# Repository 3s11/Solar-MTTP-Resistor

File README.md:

# Solar-MTTP-Resistor
Photovoltaic heater at the maximum available power.

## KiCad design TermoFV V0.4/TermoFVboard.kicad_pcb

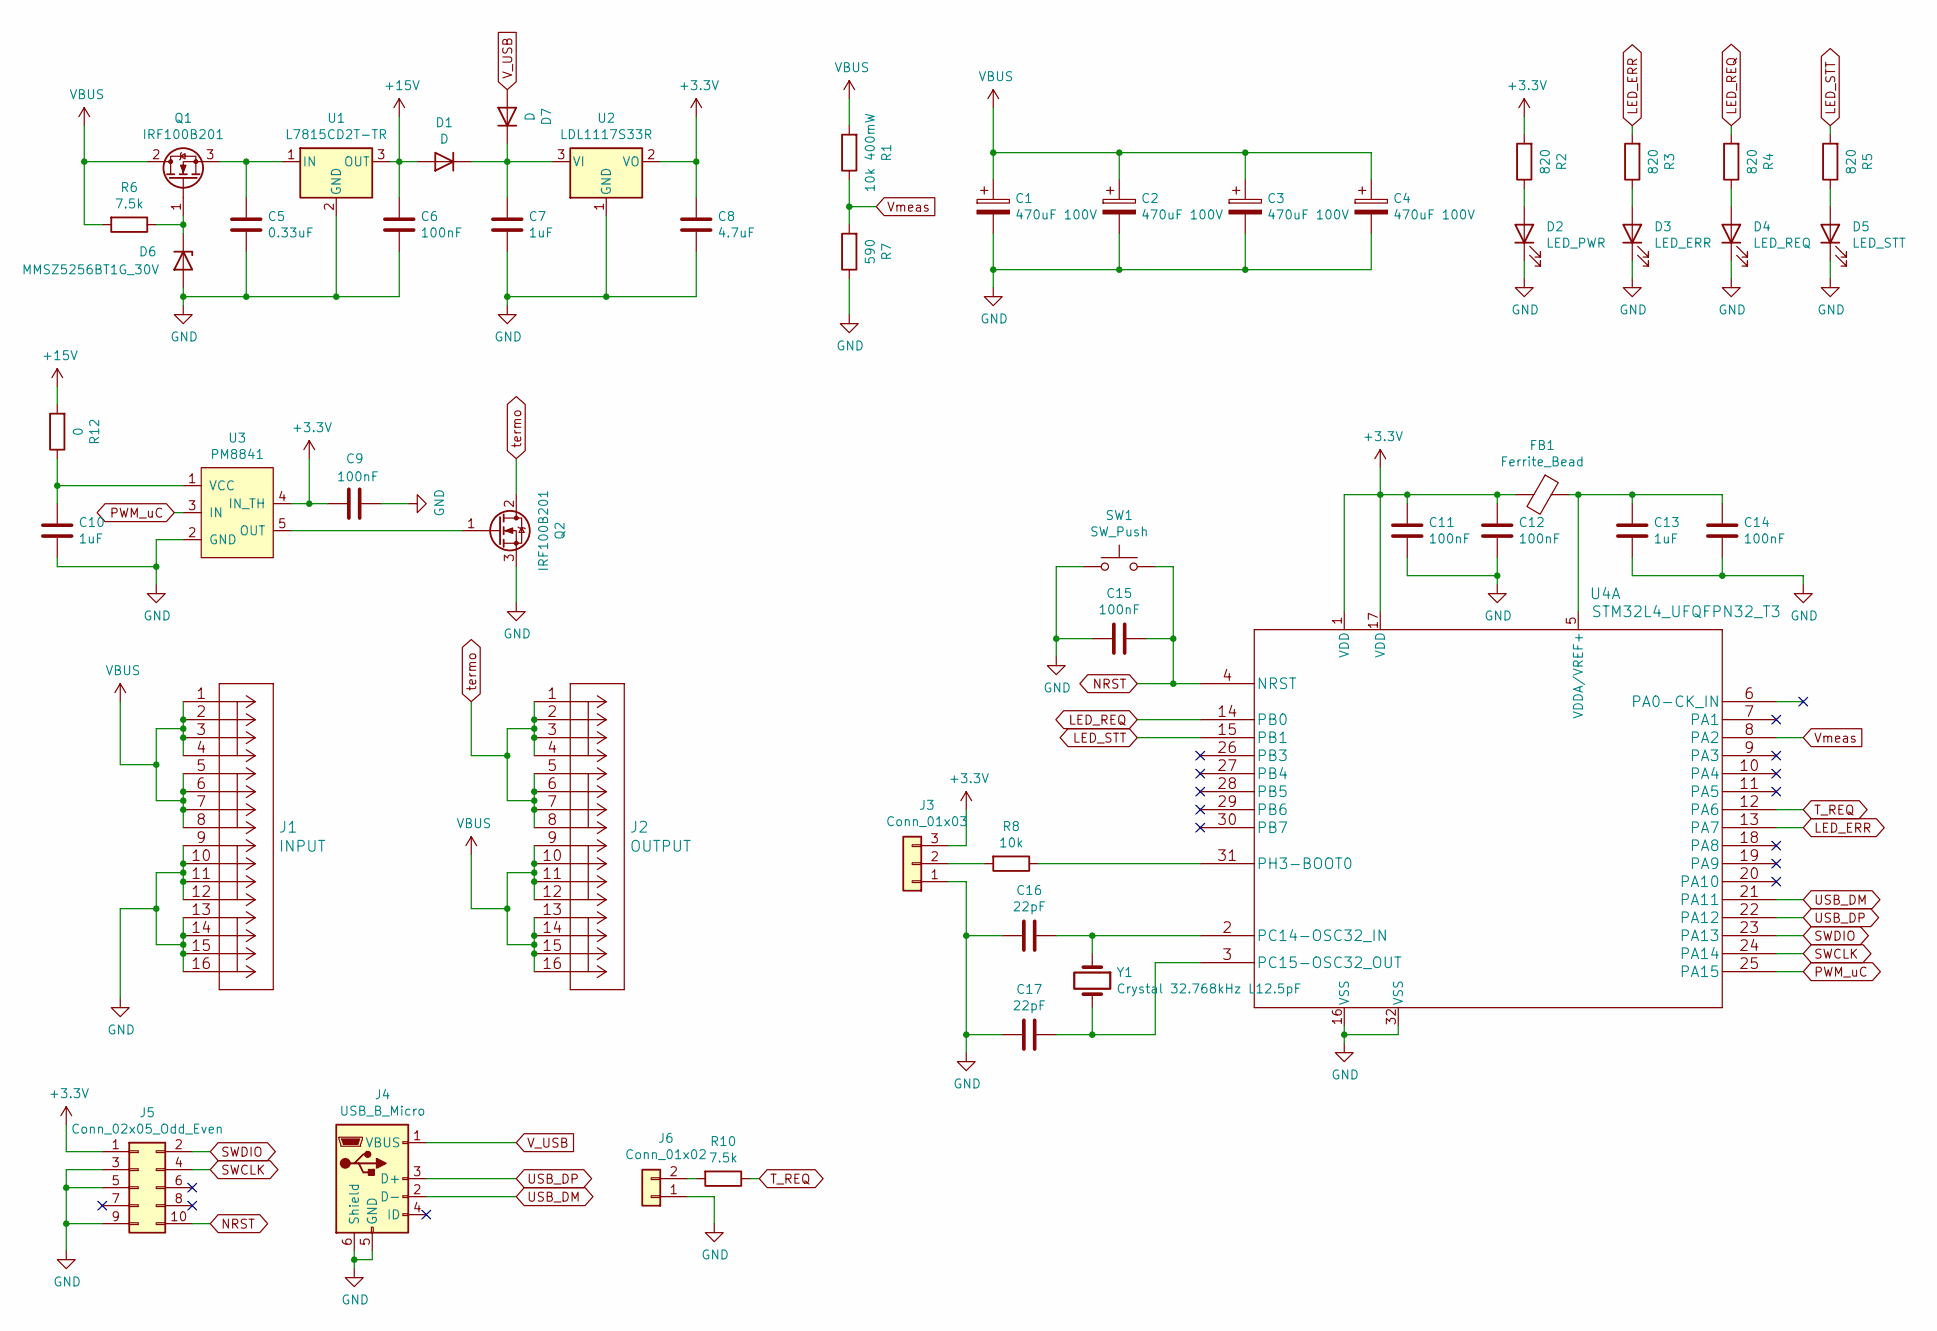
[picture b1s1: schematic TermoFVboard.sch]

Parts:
C1, C2, C3, C4: 470uF 100V; CP_Radial_D16.0mm_P7.50mm
C5: 0.33uF; C_1206_3216Metric
C6, C9, C11, C12, C14, C15: 100nF; C_1206_3216Metric
C7, C10, C13: 1uF; C_1206_3216Metric
C8: 4.7uF; C_1206_3216Metric
C16, C17: 22pF; C_1206_3216Metric
D1, D7: D; D_SMA
D2: LED_PWR; LED_1206_3216Metric
D3: LED_ERR; LED_1206_3216Metric
D4: LED_REQ; LED_1206_3216Metric
D5: LED_STT; LED_1206_3216Metric
D6: MMSZ5256BT1G_30V; D_SOD-123
FB1: Ferrite_Bead; L_1206_3216Metric
J1: INPUT; 2716-104
J2: OUTPUT; 2716-104
J3: Conn_01x03; PinHeader_1x03_P2.54mm_Vertical
J4: USB_B_Micro; USB_Micro-B_Wuerth_614105150721_Vertical
J5: Conn_02x05_Odd_Even; PinHeader_2x05_P1.27mm_Vertical
J6: Conn_01x02; PhoenixContact_MSTBVA_2,5_2-G-5,08_1x02_P5.08mm_Vertical
Q1, Q2: IRF100B201; TO-220-3_Vertical
R1: 10k 400mW; R_1206_3216Metric
R2, R3, R4, R5: 820; R_1206_3216Metric
R6, R10: 7.5k; R_1206_3216Metric
R7: 590; R_1206_3216Metric
R8: 10k; R_1206_3216Metric
R12: 0; R_1206_3216Metric
SW1: SW_Push; SW_PUSH_6mm_H7.3mm
U1: L7815CD2T-TR; TO-263-2
U2: LDL1117S33R; SOT-223-3_TabPin2
U3: PM8841; SOT-23-5
U4: STM32L4_UFQFPN32_T3; LQFP-32_7x7mm_P0.8mm
Y1: Crystal 32.768kHz L12.5pF; Crystal_SMD_3215-2Pin_3.2x1.5mm

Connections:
+3V3: C8.1, C9.1, C11.2, C12.2, FB1.2, J3.3, J5.1, R2.2, U2.2 (VO), U3.4 (IN_TH), U4.1 (VDD), U4.17 (VDD)
+15V: C6.1, D1.2 (A), R12.2, U1.3 (OUT)
GND: C1.2, C2.2, C3.2, C4.2, C5.2, C6.2, C7.2, C8.2, C9.2, C10.1, C11.1, C12.1, C13.1, C14.1, C15.2, C16.2, C17.2, D2.1 (K), D3.1 (K), D4.1 (K), D5.1 (K), D6.2 (A), J1.9, J1.10, J1.11, J1.12, J1.13, J1.14, J1.15, J1.16, J3.1, J4.5 (GND), J4.6 (Shield), J5.3, J5.5, J5.9, J6.1, Q2.3 (S), R7.1, SW1.1, U1.2 (GND), U2.1 (GND), U3.2 (GND), U4.16 (VSS), U4.32 (VSS)
LED_ERR: R3.2, U4.13 (PA7)
LED_REQ: R4.2, U4.14 (PB0)
LED_STT: R5.2, U4.15 (PB1)
NRST: C15.1, J5.10, SW1.2, U4.4 (NRST)
unnamed: C5.1, Q1.3 (S), U1.1 (IN)
unnamed: C7.1, D1.1 (K), D7.1 (K), U2.3 (VI)
unnamed: C10.2, R12.1, U3.1 (VCC)
unnamed: C13.2, C14.2, FB1.1, U4.5 (VDDA/VREF+)
unnamed: C16.1, U4.2 (PC14-OSC32_IN), Y1.1
unnamed: C17.1, U4.3 (PC15-OSC32_OUT), Y1.2
unnamed: D2.2 (A), R2.1
unnamed: D3.2 (A), R3.1
unnamed: D4.2 (A), R4.1
unnamed: D5.2 (A), R5.1
unnamed: D6.1 (K), Q1.1 (G), R6.1
unnamed: J3.2, R8.2
unnamed: J6.2, R10.2
unnamed: Q2.1 (G), U3.5 (OUT)
unnamed: R8.1, U4.31 (PH3-BOOT0)
PWM_uC: U3.3 (IN), U4.25 (PA15)
SWCLK: J5.4, U4.24 (PA14)
SWDIO: J5.2, U4.23 (PA13)
T_REQ: R10.1, U4.12 (PA6)
USB_DM: J4.2 (D-), U4.21 (PA11)
USB_DP: J4.3 (D+), U4.22 (PA12)
VBUS: C1.1, C2.1, C3.1, C4.1, J1.1, J1.2, J1.3, J1.4, J1.5, J1.6, J1.7, J1.8, J2.9, J2.10, J2.11, J2.12, J2.13, J2.14, J2.15, J2.16, Q1.2 (D), R1.2, R6.2
V_USB: D7.2 (A), J4.1 (VBUS)
Vmeas: R1.1, R7.2, U4.8 (PA2)
termo: J2.1, J2.2, J2.3, J2.4, J2.5, J2.6, J2.7, J2.8, Q2.2 (D)

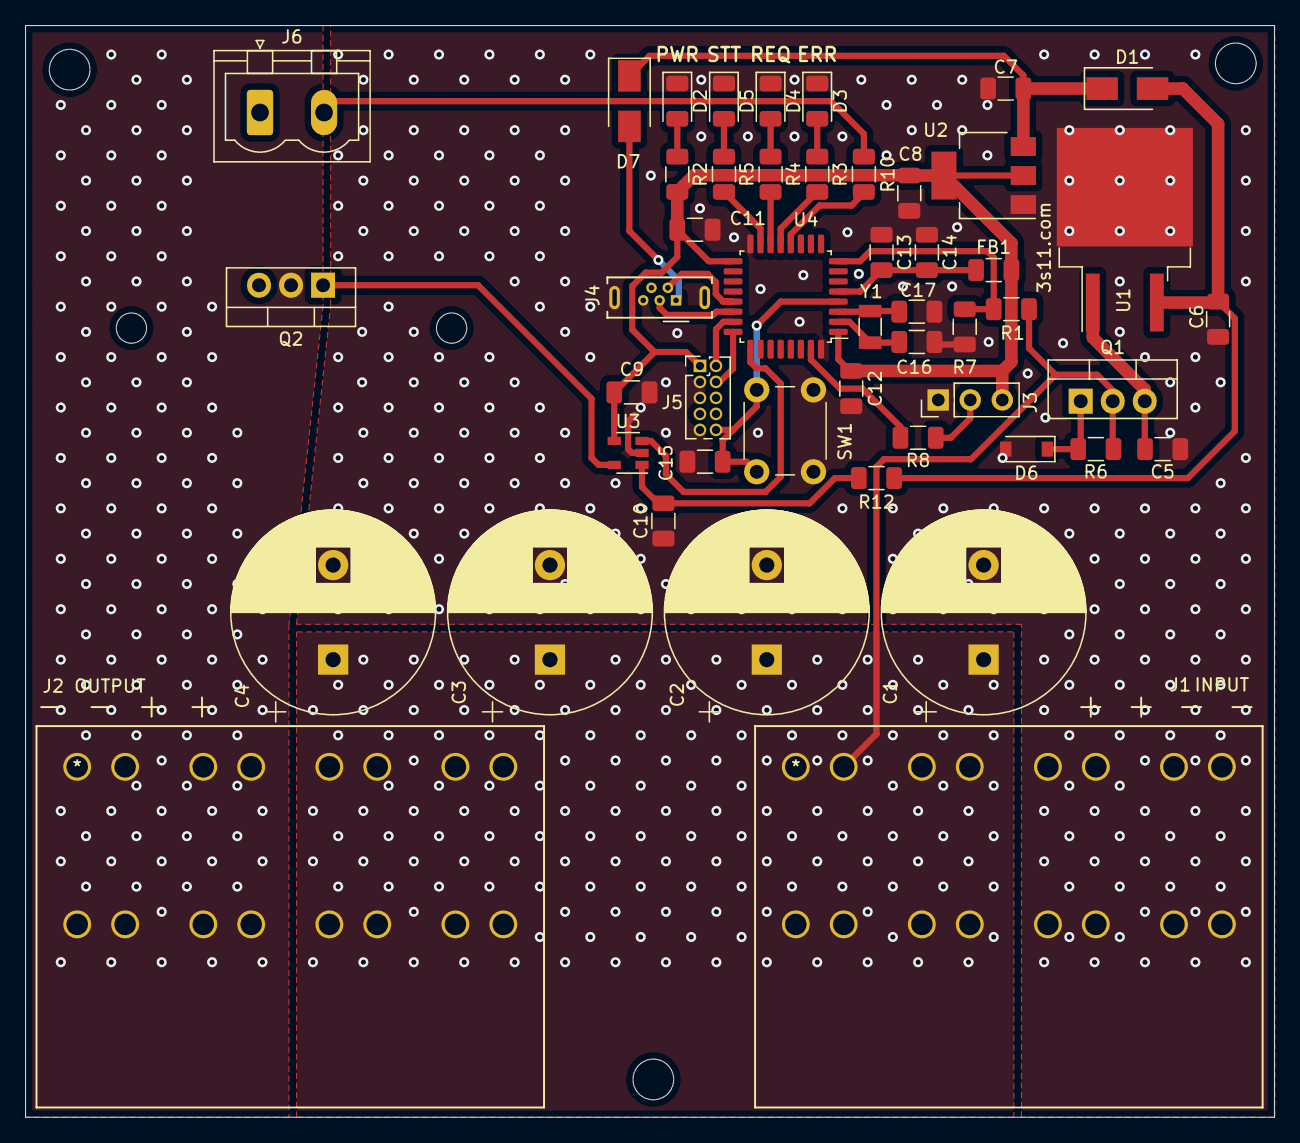
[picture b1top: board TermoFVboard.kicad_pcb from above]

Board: 2 copper layers, 99.1 x 86.6 mm, 49 parts (0 on the bottom side), 32 nets.

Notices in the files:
parts and their libraries:
Copyright 2016 Accelerated Designs. All rights reserved.
